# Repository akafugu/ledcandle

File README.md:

LED Candle Firmware & CAD files
--------------------------

Firmware and CAD filesfor the [Akafugu Flickering LED Candle](http://www.akafugu.jp/posts/products/ledcandle/)

The Akafugu LED Candle is an artificial candle that imitates the flickering of
a real candle. Use it in place of a real tea candle: It will fit
inside a tea candle casing or any holder made for tea candles.

It comes as a kit of easy to solder components, and is suitable for beginners
to soldering.

FEATURES:

* Randomly flickering LED: Imitates a candle
* Fits inside a tea candle casing
* Open Source Firmware (available at [GitHub](https://github.com/akafugu/ledcandle))
* Open Source Hardware: Eagle PCB design files available at GitHub.
* On-board ISP header for upgrading firmware

Firmware
--------

The Akafugu LED Candle uses an ATTiny13A microcontroller. The firmware is written for the
avr-gcc compiler.

See [here](http://www.akafugu.jp/posts/resources/avr-gcc/) for avr-gcc installation instructions.

Plug in ISP programmer into the ISP header, and in the directory 'firmware', do:

make fuse flash

An alternative firmware is available in the directory firmware_pwm, courtesy of madworm.
This firmware features a very different and slower flickering style.

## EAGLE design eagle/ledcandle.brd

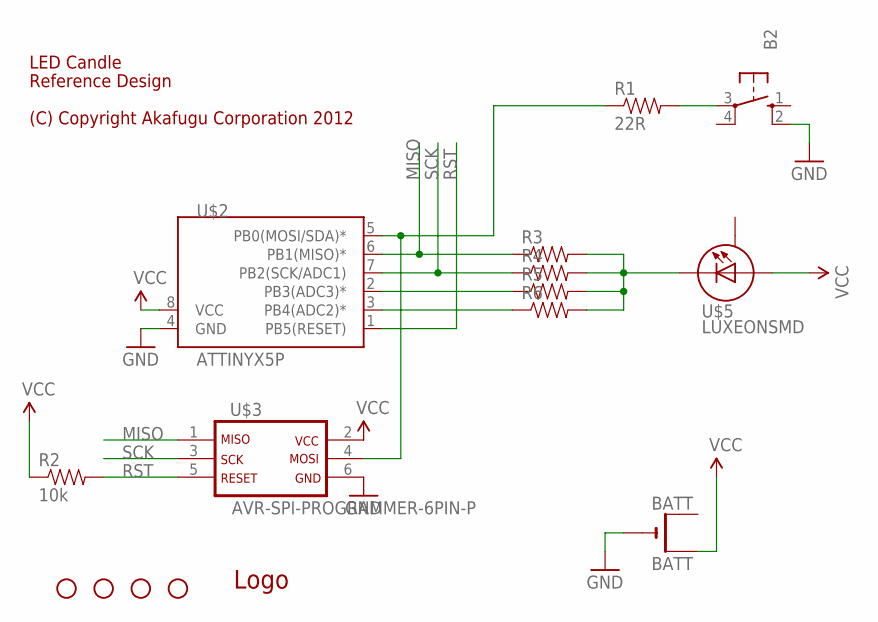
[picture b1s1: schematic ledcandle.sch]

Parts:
B2: 10-XX; B3F-10XX
BATT: BATT; CR2032-THM-PAD
JP1, JP2, JP3, JP4: STAND-OFF
R1: 22R; 1/6W-RES-OUTLINE
R2: 10k; 1/6W-RES-OUTLINE
R3, R4, R5, R6: RESISTOR-PTH-1/6W-OUTLINE; 1/6W-RES-OUTLINE
U$1: OSHW-LOGO-FILL
U$2: ATTINYX5P; DIL-8
U$3: AVR-SPI-PROGRAMMER-6PIN-P; 2X03
U$5: LUXEONSMD; LUXEON

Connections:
GND: B2.2 (S1), BATT.-, U$2.4 (GND), U$3.6
MISO: R3.1, U$2.6 (PB1(MISO)*), U$3.1
unnamed: R6.1, U$2.3 (PB4(ADC2)*)
unnamed: R3.2, R4.2, R5.2, R6.2, U$5.C
unnamed: R5.1, U$2.2 (PB3(ADC3)*)
unnamed: R1.1, U$2.5 (PB0(MOSI/SDA)*), U$3.4
RESET: B2.3, R1.2
RST: R2.2, U$2.1 (PB5(RESET)), U$3.5
SCK: R4.1, U$2.7 (PB2(SCK/ADC1)), U$3.3
VCC: BATT.+2 (+1), R2.1, U$2.8 (VCC), U$3.2, U$5.A

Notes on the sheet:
LED Candle
Reference Design
(C) Copyright Akafugu Corporation 2012

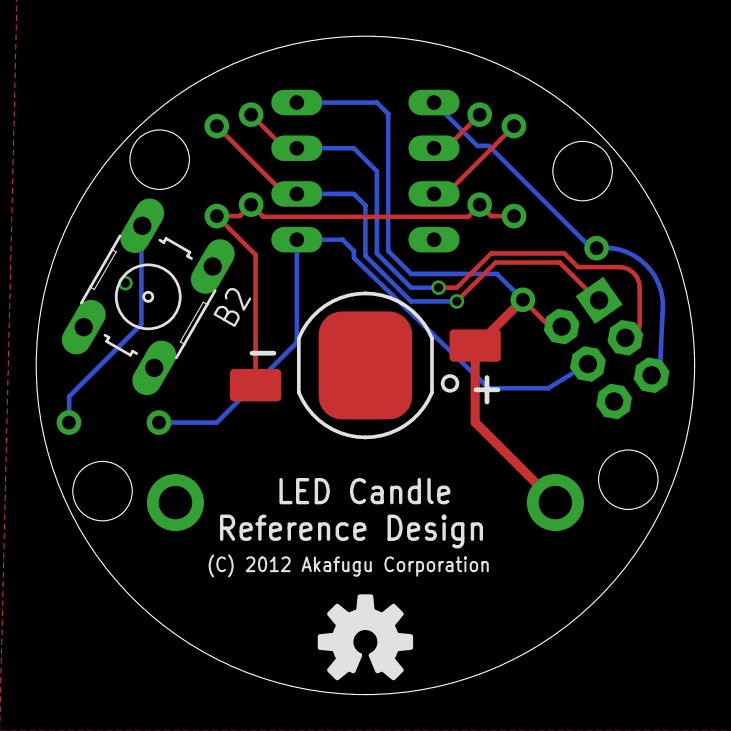
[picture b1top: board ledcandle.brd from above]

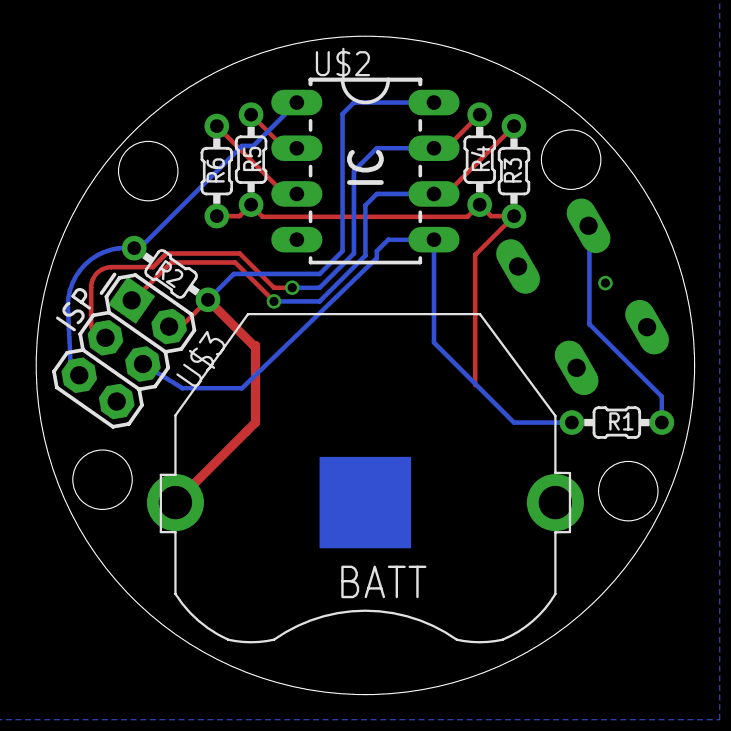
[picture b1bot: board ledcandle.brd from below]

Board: 2 copper layers, 36.6 x 36.6 mm, 16 parts (9 on the bottom side), 10 nets.

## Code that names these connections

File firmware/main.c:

/*
 * Flickering LED Candle
 * (C) 2012 Akafugu Corporation
 *
 * This program is free software; you can redistribute it and/or modify it under the
 * terms of the GNU General Public License as published by the Free Software
 * Foundation; either version 2 of the License, or (at your option) any later
 * version.
 *
 * This program is distributed in the hope that it will be useful, but WITHOUT ANY
 * WARRANTY; without even the implied warranty of MERCHANTABILITY or FITNESS FOR A
 * PARTICULAR PURPOSE.  See the GNU General Public License for more details.
 *
 */

/*
 * Pinout:
 * PB0 (pin 5) - Button (INT0 interrupt)
 * PB1 (pin 6) - LED (PWM)
 * PB2 (pin 7) - LED
 * PB3 (pin 2) - LED
 * PB4 (pin 3) - LED
 * PB5 (pin 1) - Reset
 *
 * 1k resistor per pin. Suitable for running from a 3V CR2032 cell
 *
 *
 * Inspired by similar LED candle projects on Instructables:
 *
 * http://www.instructables.com/id/YAFLC-Yet-Another-Flickering-LED-Candle/
 * http://www.instructables.com/id/Realistic-Fire-Effect-with-Arduino-and-LEDs/
 *
 */

#define BUTTON_PORT PORTB
#define BUTTON_DDR  DDRB
#define BUTTON_PIN  PINB
#define BUTTON_BIT PB0

#include <avr/io.h>
#include <avr/interrupt.h>
#include <avr/sleep.h>
#include <util/delay.h>
#include <stdbool.h>

#define sbi(var, mask)   ((var) |= (uint8_t)(1 << mask))
#define cbi(var, mask)   ((var) &= (uint8_t)~(1 << mask))

// button control
volatile bool button_held = false;

// defines for on time (in seconds)
#define ON_1H 3600
#define ON_2H 7200
#define ON_3H 10800
#define ON_4H 14400
#define ON_5h 18000

// for counting seconds
volatile uint16_t int_counter;
volatile uint16_t sec_counter;

// how long to stay on
volatile uint16_t off_timer = ON_2H;

// for hold to turn off feature
volatile uint16_t button_held_counter; // how long has button been held?
volatile bool off_flag = false; // has the button been held long enough to turn off?

// for flickering intensity
volatile bool fast_flicker = true;

void led_off(void)
{
	PORTB = 0xff;
	DDRB = 0b11111110;
}

void led_on(void)
{
	PORTB = 0x1; // keep pull-up for button set
	DDRB = 0b11111110;
}

// random number seed (will give same flicker sequence each time)
volatile uint32_t lfsr = 0xbeefcace;

uint32_t rand(void)
{
	// http://en.wikipedia.org/wiki/Linear_feedback_shift_register
	// Galois LFSR: taps: 32 31 29 1; characteristic polynomial: x^32 + x^31 + x^29 + x + 1 */
  	lfsr = (lfsr >> 1) ^ (-(lfsr & 1u) & 0xD0000001u);
	return lfsr;
}

// Enter sleep mode: Wake on INT0 interrupt
void do_sleep(void)
{
	led_off();

	GIMSK |= (1<<PCIE); // Pin change interrupt enabled
	PCMSK |= 1<<PCINT0;

	sei();
	set_sleep_mode(_BV(SM1)); // Power down sleep mode (sets MCUCR)
	sleep_mode();

	off_timer = ON_2H;
}

// Interrupt signal PCINT0: On PB0
ISR (PCINT0_vect)
{
	cli();
}

// Flicker by randomly setting pins PB1~PB4 on and off
void flicker(void)
{
	uint32_t r;
	uint8_t temp;

	// Inititalize timer
	TCCR0B = (1<<CS01); // Set Prescaler to clk/8 : 1 click = aprox 2us (using 4.6MHz internal clock)
	TIMSK0 |= (1<<TOIE0); // Enable Overflow Interrupt Enable
	TCNT0 = 0; // Initialize counter

	// LED off
	PORTB = 0xff;
	// PB0 as input
	DDRB = 0b11111110;
	// enable PB0 pull-up
	BUTTON_PORT |= _BV(BUTTON_BIT);

	GIMSK |= (1<<PCIE); // Pin change interrupt enabled
	PCMSK |= 1<<PCINT0;

	while(1)
	{
		r = rand();

		if (off_flag) {
			led_off();
		}
		else {
			temp = (uint8_t)r; // use lowermost 8 bits to set values for the LED pins

			// set PB1~PB4 according to value of temp
			if (temp & 1) { // off
				cbi(DDRB, PB1);
				sbi(PORTB, PB1);
			}
			else { // on
				sbi(DDRB, PB1);
				cbi(PORTB, PB1);
			}

			if (temp & (1<<1)) { // off
				cbi(DDRB, PB2);
				sbi(PORTB, PB2);
			}
			else { // on
				sbi(DDRB, PB2);
				cbi(PORTB, PB2);
			}
			
			if (fast_flicker) {
				if (temp & (1<<2)) { // off
					cbi(DDRB, PB3);
					sbi(PORTB, PB3);
				}
				else { // on
					sbi(DDRB, PB3);
					cbi(PORTB, PB3);
				}
			}
			else {
				sbi(DDRB, PB3);
				cbi(PORTB, PB3);
			}

			// Keep at least one pin on at all times to keep LED from turning off completely
			sbi(DDRB, PB4);
			cbi(PORTB, PB4);
		}

		// Use top byte to control delay between each intensity change
		// Tweaking these numbers will affect the speed of the flickering
		temp = (uint8_t) (r >> 24);
		_delay_loop_2(temp<<7);
	} 
}

// 1 click = aprox 2us*8 = 16us
// interrupt runs every 256 clicks = every 4096 us = 0.004096 seconds
// 244 interrupts = aprox 1 second ideally
// actual value tweaked to match CPU load
ISR(TIM0_OVF_vect)
{
	if (++int_counter == 285) { // count seconds
		sec_counter++;
		int_counter = 0;
	}
	
	if (BUTTON_PIN & _BV(BUTTON_BIT)) { // button is not held
		if (button_held_counter > 0) { // button up detected
			fast_flicker = !fast_flicker; 
		}

		button_held = false;
		button_held_counter = 0;
	}
	else { // button is held
		button_held = true;
		button_held_counter++;
	}

	// time to go to sleep?
	if (off_timer != 0 && sec_counter >= off_timer && !button_held) {
		sec_counter = 0;
		off_flag = false;
		button_held_counter = 0;
		do_sleep();
		return;
	}
	
	// holding the button for 3 seconds turns the device off
	if (button_held_counter == 570) {
		off_flag = true;
		return;
	}
	
	// when off flag is set, wait for key up to go to sleep (otherwise the interrupt pin will wake the device up again)
	if (off_flag && !button_held) {
		off_flag = false;
		do_sleep();
	}
}

void main(void) __attribute__ ((noreturn));

void main(void)
{
	sei();
	flicker();
	while(1) {}
}

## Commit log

2012-04-15 Initial version
2012-04-21 Added high/low flicker intensity setting
2012-04-23 Added eagle CAD files
2012-11-22 Added .gitignore file
2013-04-25 First doodles for my alternative PWM-firmware.
2013-04-25 So far so good. Need button debouncing!
2013-04-25 Getting there...
2013-04-26 Code cleanup
2013-04-26 Added crude anti-bounce check for the button in do_sleep().
2013-04-26 More cleanup.
2013-04-26 There is a weird not-waking-up issue...
2013-04-26 Trying something else with sleeping.
2013-04-26 Working better now.
2013-04-26 Removed the 'fast_flicker' option for now, added garbage collect.
2013-04-26 Replaced fade_in() and fade_out() with fade(from,to);
2013-04-26 Added a delay parameter to fade();
2013-04-26 Now fading between random brightness changes. Looks good ;-)
2013-04-26 Added a readme file.
2013-04-26 Tweaks.
2013-04-27 Added a few comments.
2013-04-27 9.6MHz --> 4.8MHz + CLKPR adjusted to get 600kHz system-clock again.
2013-05-07 Fixed a typo in main.c
2013-05-07 Last adjustmenst, so the PWM firmware runs on the real hardware as well.
2013-05-07 Updated 'readme.txt'
2013-05-07 PC-interrupt enabled later. Fixed hangs after button press before sleep.
2013-05-07 Moved some #defines to 'main.h' and added more comments.
2013-05-07 Added more comments.
2013-05-11 Introduced the MIN_BRIGHTNESS #define.
2013-05-21 Added a comment.
2013-06-04 Mention alternate FW in README and minor cleanup
